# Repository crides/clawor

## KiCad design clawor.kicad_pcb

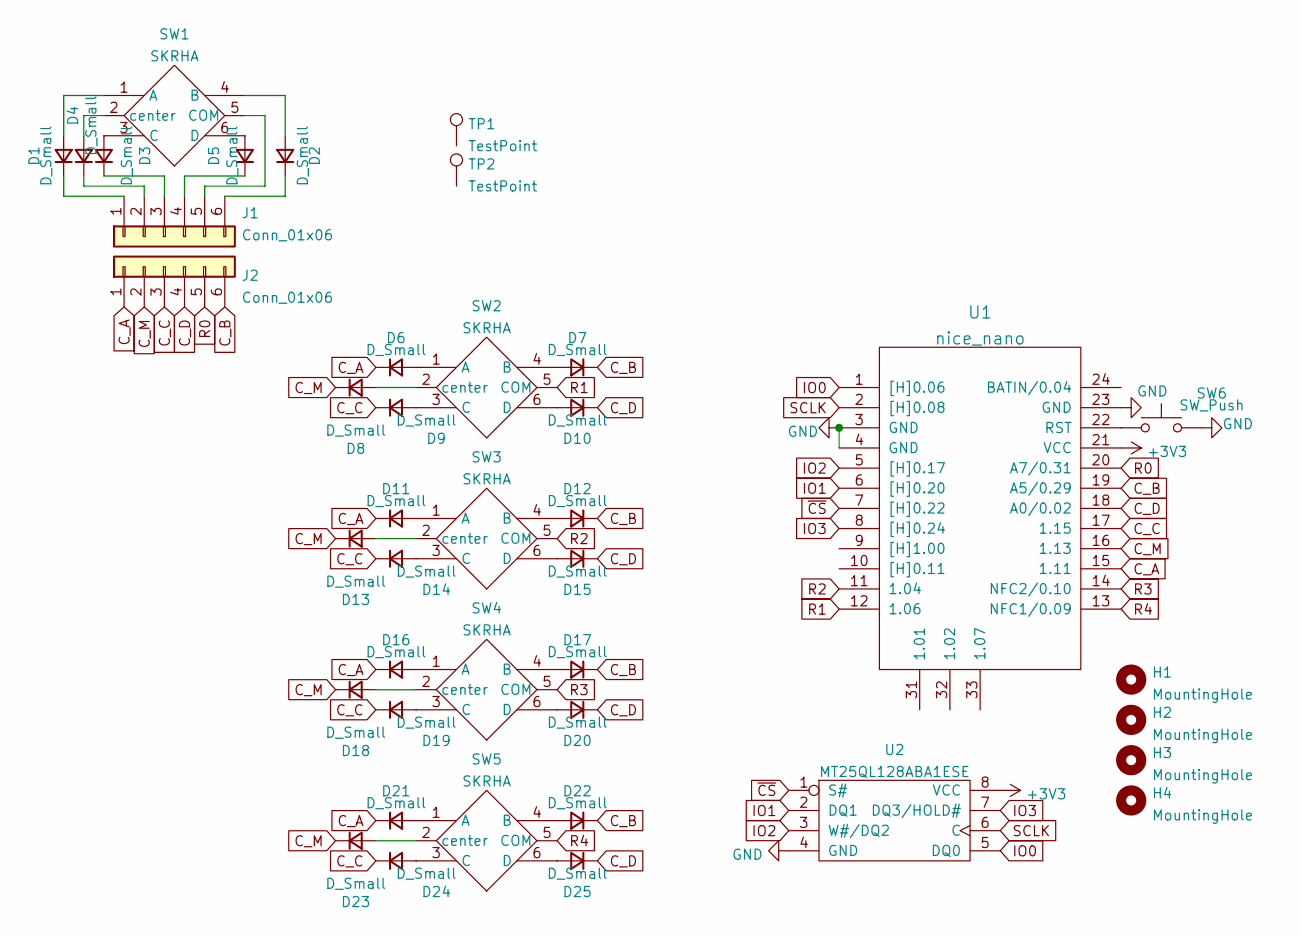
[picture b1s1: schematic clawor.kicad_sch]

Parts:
D1, D2, D3, D4, D5, D6, D7, D8, D9, D10, D11, D12, D13, D14, D15, D16, D17, D18, D19, D20, D21, D22, D23, D24, D25: D_Small; D_SOD-123
H1, H2: MountingHole; breakaway-mousebites
H3, H4: MountingHole; MountingHole_2mm
J1, J2: Conn_01x06; conn
SW1, SW2, SW3, SW4, SW5: SKRHA; SKRHA-boss
SW6: SW_Push; SW_SPST_TL3342
TP1, TP2: TestPoint; TestPoint_Pad_D2.0mm
U1: nice_nano
U2: MT25QL128ABA1ESE; SOIC-8_5.23x5.23mm_P1.27mm

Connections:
+3V3: U1.21 (VCC), U2.8 (VCC)
C_A: D6.1 (K), D11.1 (K), D16.1 (K), D21.1 (K), J2.1, U1.15 (1.11)
C_B: D7.1 (K), D12.1 (K), D17.1 (K), D22.1 (K), J2.6, U1.19 (A5/0.29)
C_C: D9.1 (K), D14.1 (K), D19.1 (K), D24.1 (K), J2.3, U1.17 (1.15)
C_D: D10.1 (K), D15.1 (K), D20.1 (K), D25.1 (K), J2.4, U1.18 (A0/0.02)
C_M: D8.1 (K), D13.1 (K), D18.1 (K), D23.1 (K), J2.2, U1.16 (1.13)
GND: SW6.2, U1.3 (GND), U1.4 (GND), U1.23 (GND), U2.4 (GND)
IO0: U1.1 ([H]0.06), U2.5 (DQ0)
IO1: U1.6 ([H]0.20), U2.2 (DQ1)
IO2: U1.5 ([H]0.17), U2.3 (W#/DQ2)
IO3: U1.8 ([H]0.24), U2.7 (DQ3/HOLD#)
unnamed: D1.1 (K), J1.1
unnamed: D1.2 (A), SW1.1 (A)
unnamed: D2.1 (K), J1.6
unnamed: D2.2 (A), SW1.4 (B)
unnamed: D3.1 (K), J1.2
unnamed: D3.2 (A), SW1.2 (center)
unnamed: D4.1 (K), J1.3
unnamed: D4.2 (A), SW1.3 (C)
unnamed: D5.1 (K), J1.4
unnamed: D5.2 (A), SW1.6 (D)
unnamed: D6.2 (A), SW2.1 (A)
unnamed: D7.2 (A), SW2.4 (B)
unnamed: D8.2 (A), SW2.2 (center)
unnamed: D9.2 (A), SW2.3 (C)
unnamed: D10.2 (A), SW2.6 (D)
unnamed: D11.2 (A), SW3.1 (A)
unnamed: D12.2 (A), SW3.4 (B)
unnamed: D13.2 (A), SW3.2 (center)
unnamed: D14.2 (A), SW3.3 (C)
unnamed: D15.2 (A), SW3.6 (D)
unnamed: D16.2 (A), SW4.1 (A)
unnamed: D17.2 (A), SW4.4 (B)
unnamed: D18.2 (A), SW4.2 (center)
unnamed: D19.2 (A), SW4.3 (C)
unnamed: D20.2 (A), SW4.6 (D)
unnamed: D21.2 (A), SW5.1 (A)
unnamed: D22.2 (A), SW5.4 (B)
unnamed: D23.2 (A), SW5.2 (center)
unnamed: D24.2 (A), SW5.3 (C)
unnamed: D25.2 (A), SW5.6 (D)
unnamed: J1.5, SW1.5 (COM)
unnamed: SW6.1, U1.22 (RST)
R0: J2.5, U1.20 (A7/0.31)
R1: SW2.5 (COM), U1.12 (1.06)
R2: SW3.5 (COM), U1.11 (1.04)
R3: SW4.5 (COM), U1.14 (NFC2/0.10)
R4: SW5.5 (COM), U1.13 (NFC1/0.09)
SCLK: U1.2 ([H]0.08), U2.6 (C)
~CS: U1.7 ([H]0.22), U2.1 (S#)

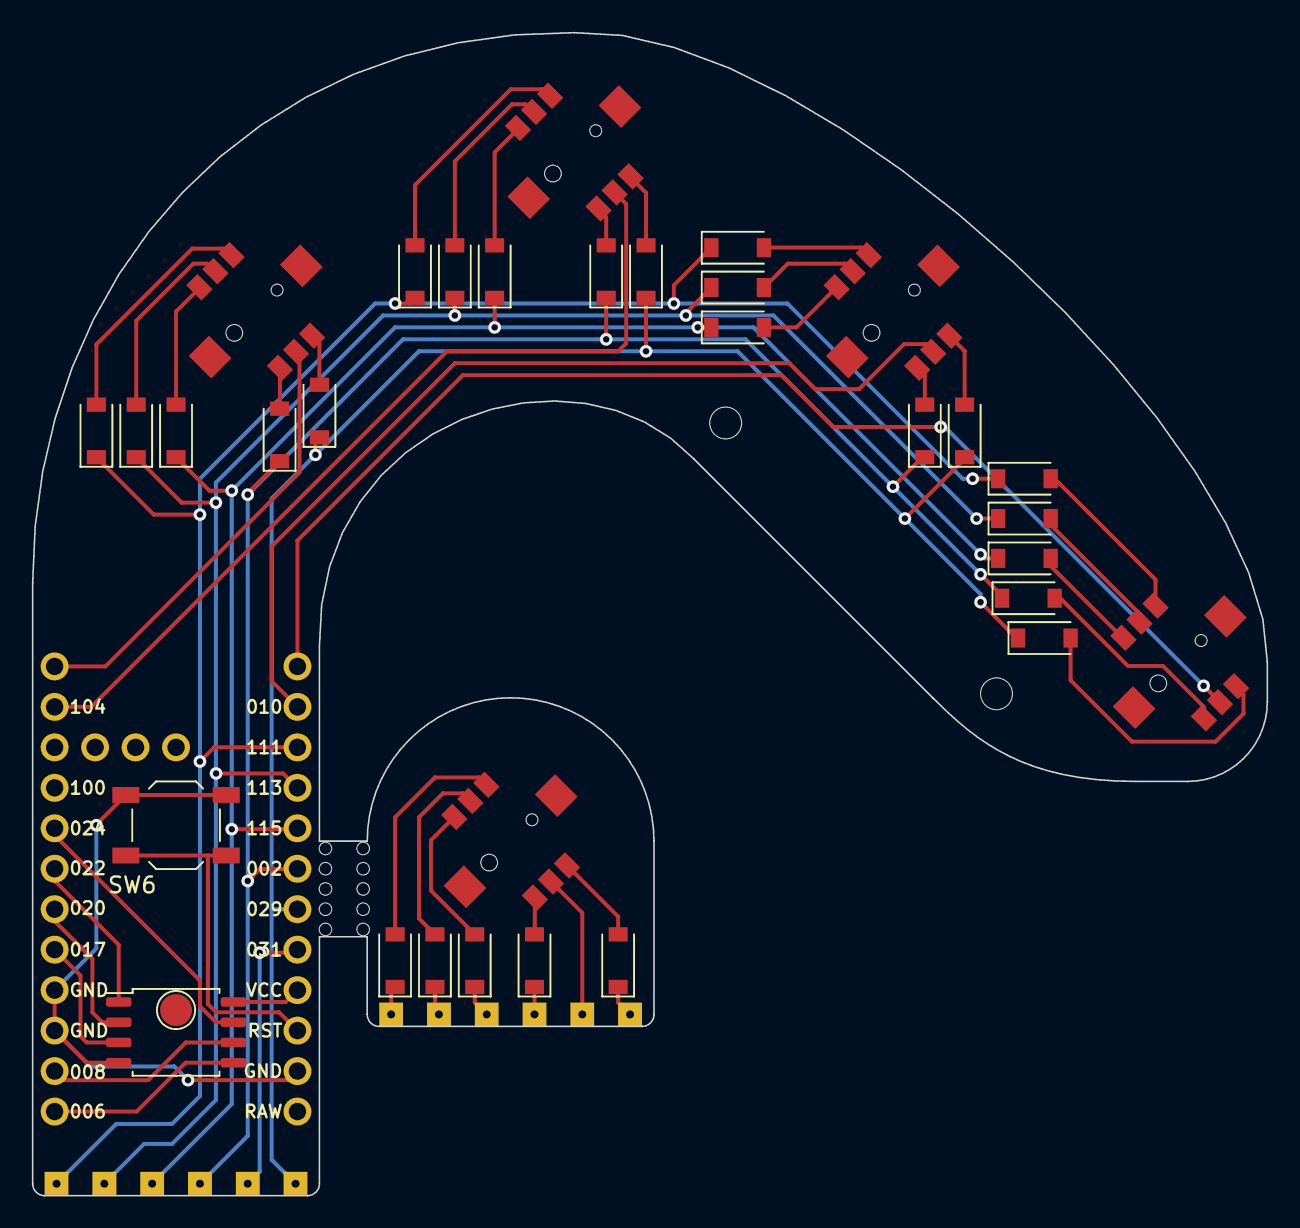
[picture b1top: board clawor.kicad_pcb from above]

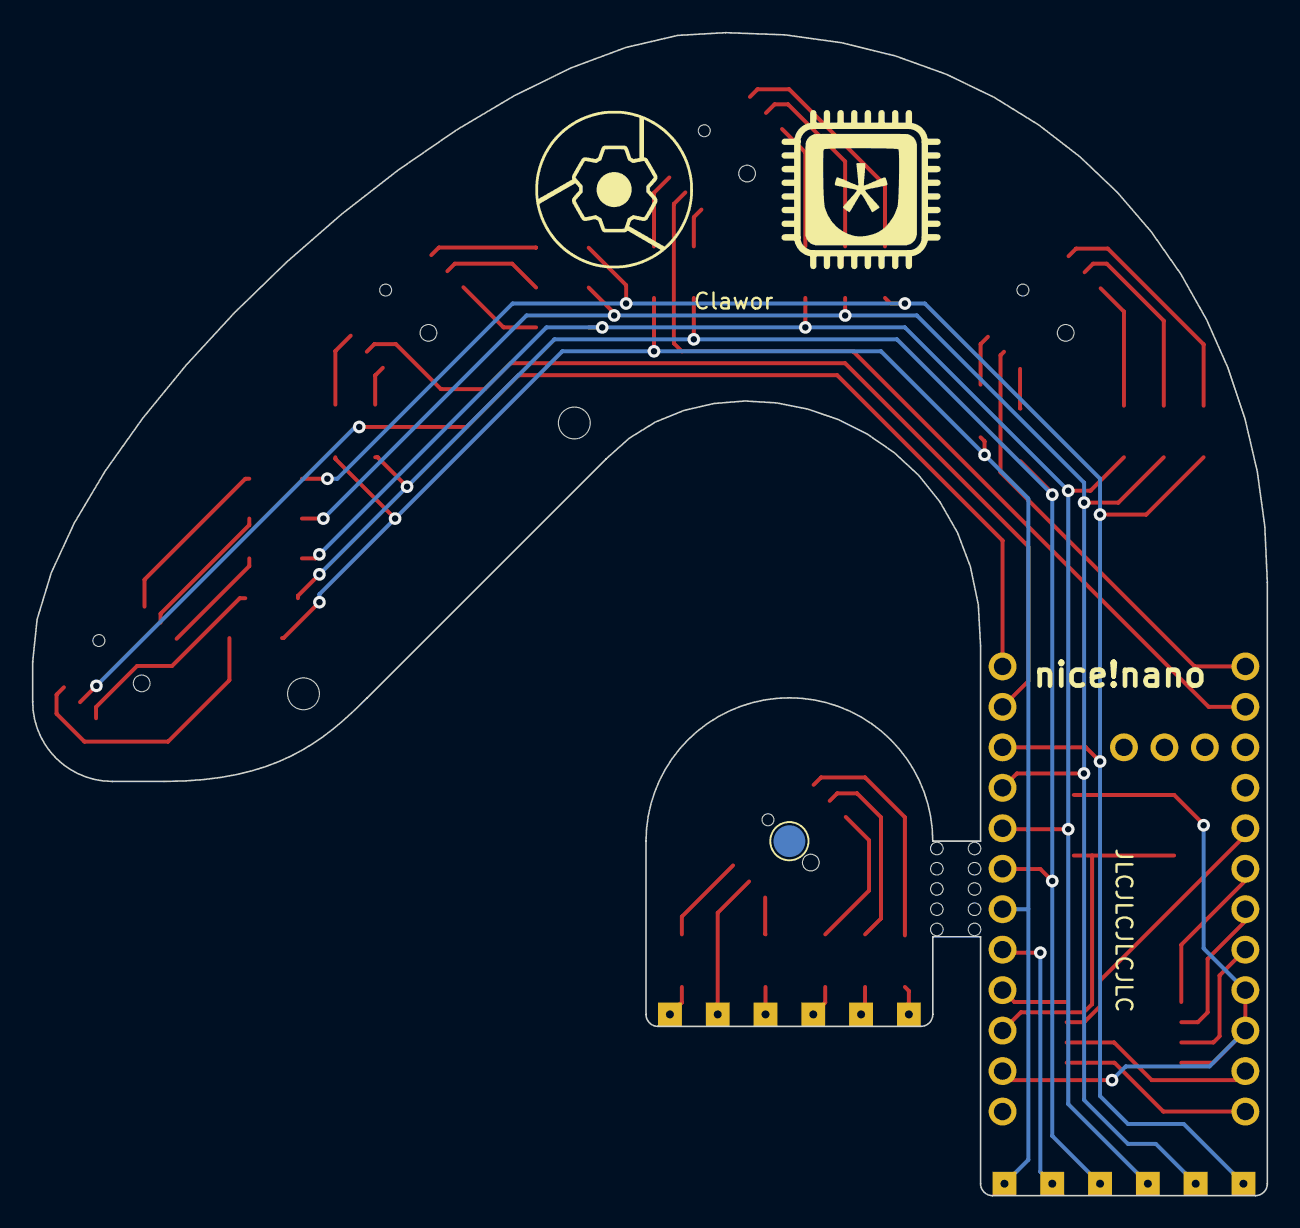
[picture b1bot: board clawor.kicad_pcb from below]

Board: 2 copper layers, 77.5 x 73.0 mm, 41 parts (2 on the bottom side), 50 nets.

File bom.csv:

Comment,Designator,Footprint,LCSC
D_Small,"D1,D2,D3,D4,D5,D6,D7,D8,D9,D10,D11,D12,D13,D14,D15,D16,D17,D18,D19,D20,D21,D22,D23,D24,D25",Diode_SMD:D_SOD-123,
MountingHole,"H1,H2",Keebio-Parts:breakaway-mousebites,
Conn_01x06,"J1,J2",clawor:conn,
SW_Push,SW6,Button_Switch_SMD:SW_SPST_TL3342,
nice_nano,U1,nice-nano-kicad:nice_nano,
MT25QL128ABA1ESE,U2,Package_SO:SOIC-8_5.23x5.23mm_P1.27mm,

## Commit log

2022-01-09 init
